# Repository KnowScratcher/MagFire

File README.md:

# MagFire

<p align="center">
Fire!!!
</p>

# BOM
| Item                       | Amount | Price(USD) | Total(USD) | Total(TWD) |
| -------------------------- | ------ | ---------- | ---------- | ---------- |
| DC-DC 390v Transformer     | 1      | 4.85       | 4.85       | 145        |
| Copper wire (0.5mm)        | ?      | ?          | ?          |            |
| Button                     | 2      | 0.3        | 0.6        | 20         |
| Voltage indicator(dc 400v) | 0~1    | ?          | ?          | ?          |
| Capacitor 1000uF 400v      | 1      | 7.45       | 7.45       | 220        |
| Custom PCB                 | 1      | 2~4        | 4          | 60         |
| Iron ball (D=10mm)         | 1      | 0.17       | 0.17       | 5          |
| Total                      |        |            | 17.07      | 450        |

# Journal
The journal is in [JOURNAL.md](JOURNAL.md)

## How it all started?

I'm inspired by some youtuber making coil gun. So I decided to make one myself.

## What will it do?
it's a toy that fires little metal ball. basically you can charge it with a battery and when you press fire, the ball will shoot out.

- store energy in a capacitor
- fire a metal ball when the button is pressed

# Design
## Schematic

## PCB

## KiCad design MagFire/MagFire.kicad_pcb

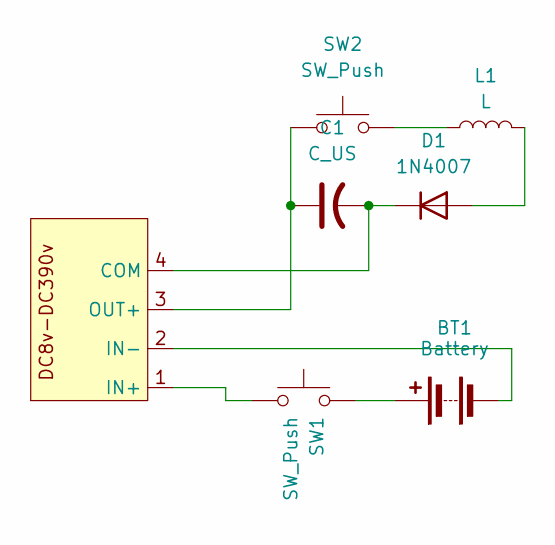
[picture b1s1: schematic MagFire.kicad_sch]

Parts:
BT1: Battery; SolderWire-0.75sqmm_1x02_P7mm_D1.25mm_OD3.5mm
C1: C_US; CP_Radial_D35.0mm_P10.00mm_SnapIn
D1: 1N4007; D_DO-41_SOD81_P10.16mm_Horizontal
L1: L; SolderWire-0.75sqmm_1x02_P7mm_D1.25mm_OD3.5mm
SW1, SW2: SW_Push; SolderWire-0.75sqmm_1x02_P7mm_D1.25mm_OD3.5mm
U1: (no value)

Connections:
unnamed: BT1.1 (+), SW1.2
unnamed: BT1.2 (-), U1.2 (IN-)
unnamed: D1.2 (A), L1.2
unnamed: C1.2, D1.1 (K), U1.4 (COM)
unnamed: L1.1, SW2.2
unnamed: SW1.1, U1.1 (IN+)
unnamed: C1.1, SW2.1, U1.3 (OUT+)

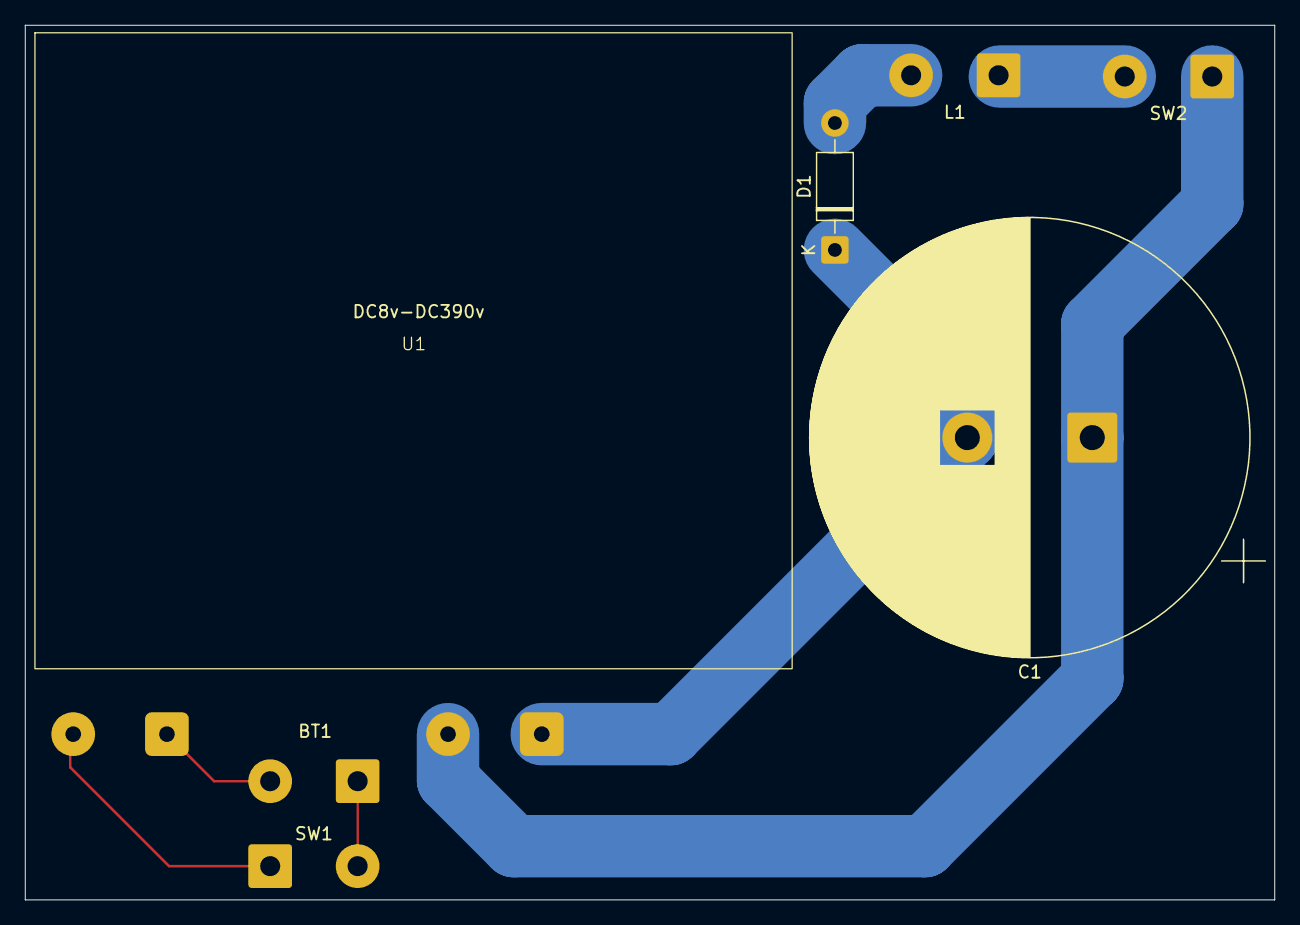
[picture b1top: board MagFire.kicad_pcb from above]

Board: 2 copper layers, 100.0 x 70.0 mm, 7 parts (0 on the bottom side), 7 nets.

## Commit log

2025-05-29 init
2025-05-30 20250530
2025-05-30 add image
2025-06-01 20250601
2025-06-02 add 20250602 journal, missing image
2025-06-05 add image and update BOM
2025-06-05 fix date
2025-06-08 add journal
2025-06-08 fix journal
2025-06-12 update model and pcb and journal
2025-06-20 update everything
2025-06-20 update journal
2025-06-24 fix readme
